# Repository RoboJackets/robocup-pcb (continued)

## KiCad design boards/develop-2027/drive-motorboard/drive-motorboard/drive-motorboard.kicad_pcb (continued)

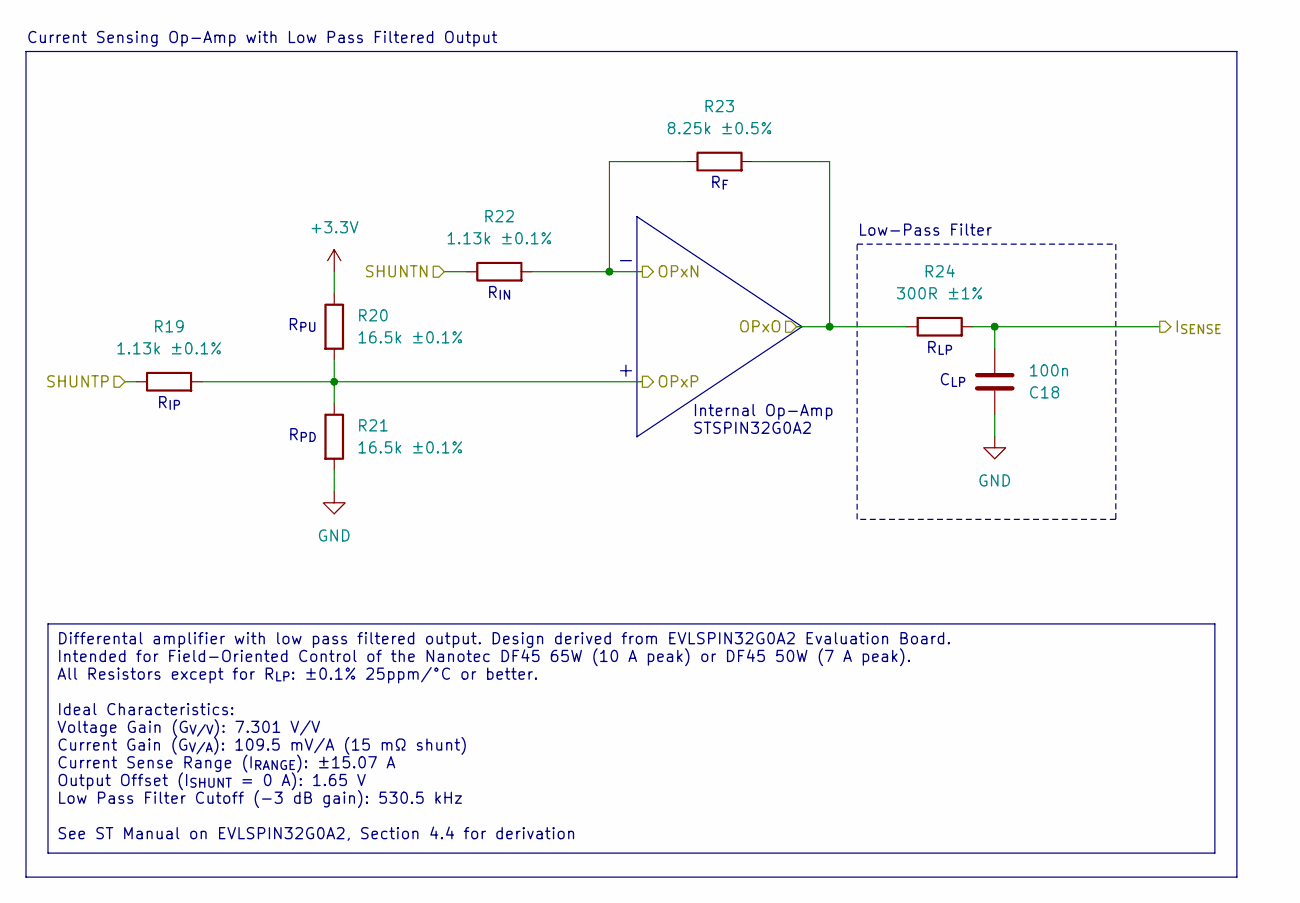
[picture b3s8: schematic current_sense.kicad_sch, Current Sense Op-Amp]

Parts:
C18: 100n; C_0402_1005Metric; Manufacturer P/N CL05B102KB5NNNC
R19, R22: 1.13k ±0.1%; R_0402_1005Metric; Manufacturer P/N RT0402BRD071K13L
R20, R21: 16.5k ±0.1%; R_0402_1005Metric; Manufacturer P/N RT0402BRD0716K5L
R23: 8.25k ±0.5%; R_0201_0603Metric; Manufacturer P/N RC0201DR-078K25L
R24: 300R ±1%; R_0201_0603Metric; Manufacturer P/N RC0201FR-07300RL

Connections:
+3.3V: R20.1; also elsewhere on the board
/Motor Controller/Current Sensing/OPxN: R22.2, R23.1; also elsewhere on the board
/Motor Controller/Current Sensing/OPxO: R23.2, R24.1; also elsewhere on the board
/Motor Controller/Current Sensing/OPxP: R19.2, R20.2, R21.1; also elsewhere on the board
/Motor Controller/I_{SENSE}: C18.2, R24.2; also elsewhere on the board
/Motor Controller/SHUNTN: R22.1; also elsewhere on the board
/Motor Controller/SHUNTP: R19.1; also elsewhere on the board
GND: C18.1, R21.2; also elsewhere on the board

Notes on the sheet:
R_{PU}
C_{LP}
Low-Pass Filter
R_{F}
R_{PD}
R_{IP}
Current Sensing Op-Amp with Low Pass Filtered Output
Internal Op-Amp STSPIN32G0A2
R_{LP}
R_{IN}
Differental amplifier with low pass filtered output. Design derived from EVLSPIN32G0A2 Evaluation Board. Intended for Field-Oriented Control of the Nanotec DF45 65W (10 A peak) or DF45 50W (7 A peak). All Resistors except for R_{LP}: ±0.1% 25ppm/°C or better. Ideal Characteristics: Voltage Gain (G_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

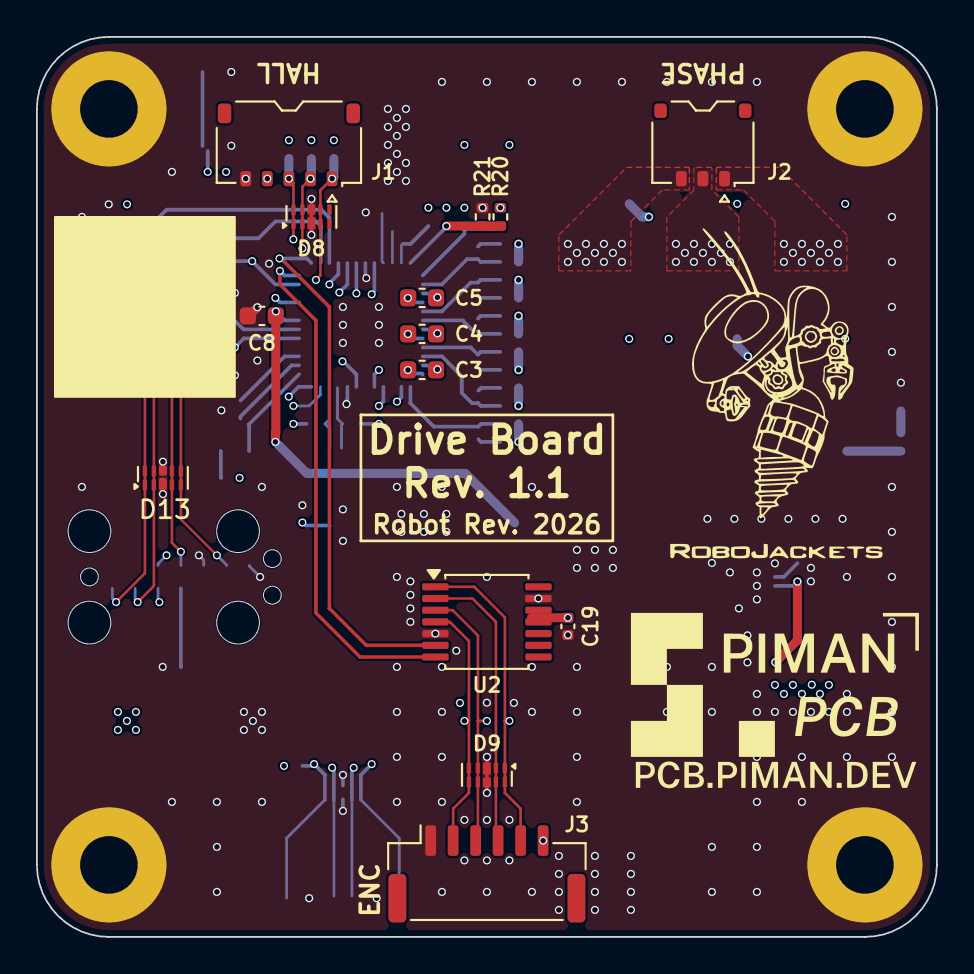
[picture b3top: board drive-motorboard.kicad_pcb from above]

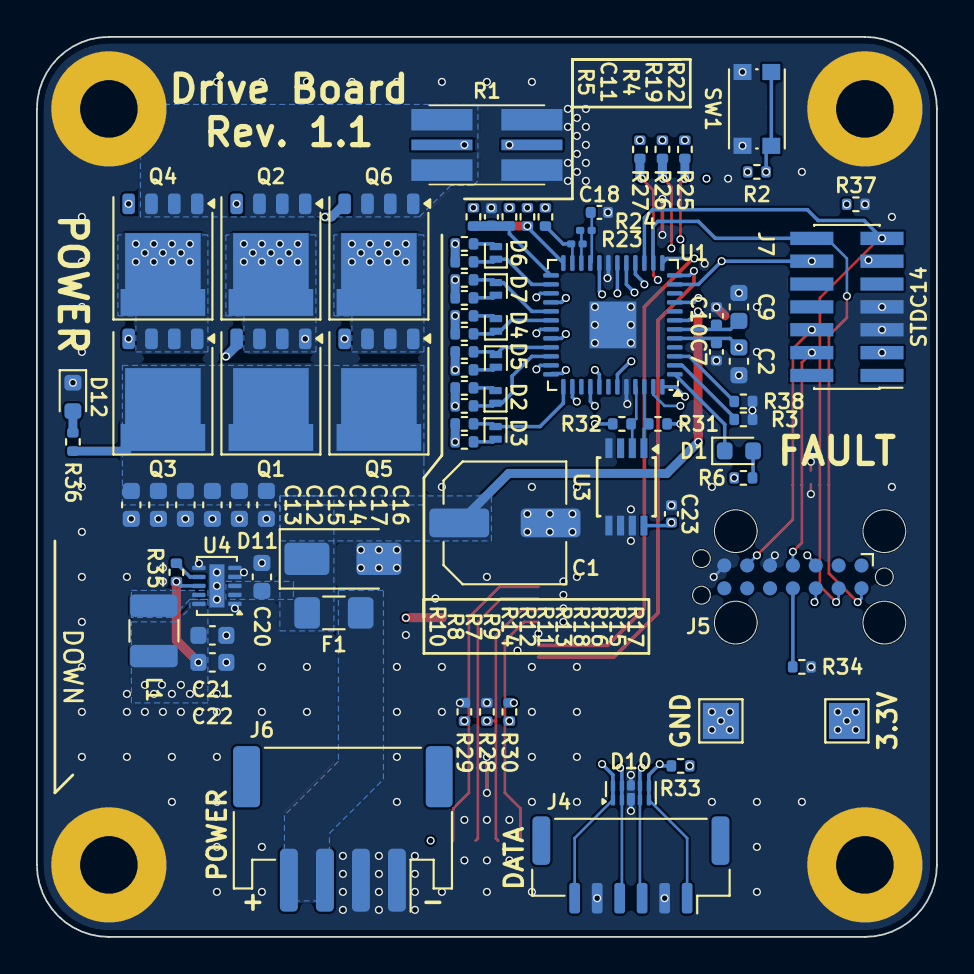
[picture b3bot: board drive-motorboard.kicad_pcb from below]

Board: 6 copper layers, 50.0 x 50.0 mm, 99 parts (81 on the bottom side), 66 nets.

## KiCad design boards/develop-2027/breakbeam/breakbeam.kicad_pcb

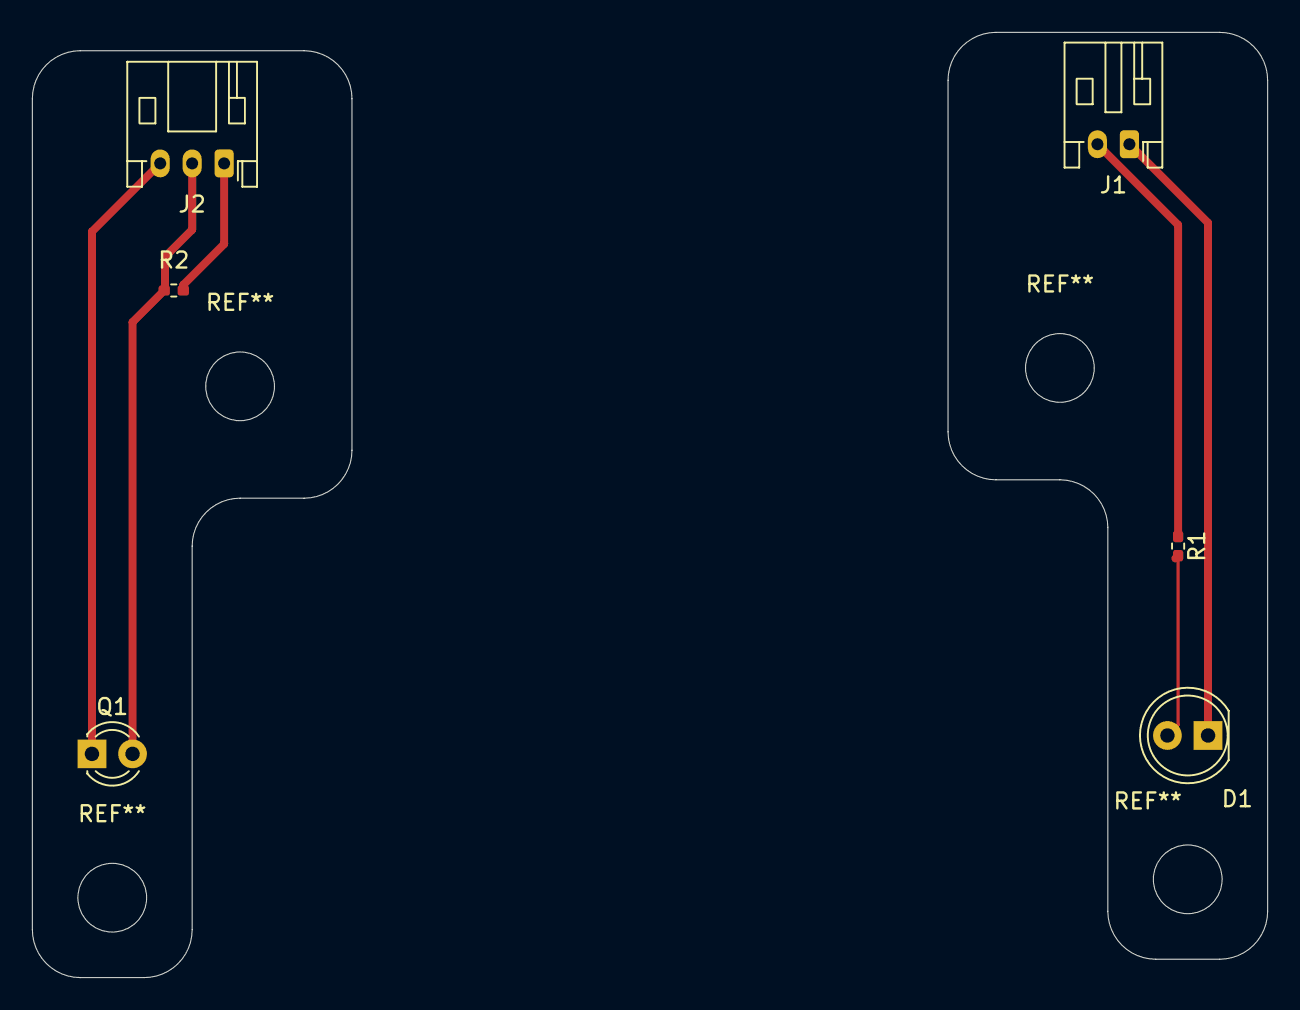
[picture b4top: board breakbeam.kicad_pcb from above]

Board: 2 copper layers, 77.3 x 59.2 mm, 6 parts (0 on the bottom side), 6 nets.

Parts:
D1: LED; LED_D5.0mm
J1: Conn_01x02; JST_PH_S2B-PH-K_1x02_P2.00mm_Horizontal
J2: Conn_01x03; JST_PH_S3B-PH-K_1x03_P2.00mm_Horizontal
Q1: TEPT4400; LED_D3.0mm_Clear
R1: 100; R_0402_1005Metric_Pad0.72x0.64mm_HandSolder
R2: 100k; R_0402_1005Metric_Pad0.72x0.64mm_HandSolder

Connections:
unnamed: D1.2 (A), R1.2
unnamed: D1.1 (K), J1.1
unnamed: J1.2, R1.1
unnamed: J2.1, R2.1
unnamed: J2.2, Q1.2 (E), R2.2
unnamed: J2.3, Q1.1 (C)

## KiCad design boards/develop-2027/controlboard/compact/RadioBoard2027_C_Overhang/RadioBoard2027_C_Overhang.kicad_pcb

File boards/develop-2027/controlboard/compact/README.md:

# Compact board set (ControlBoard2027_C4L2 + 30 x 40 radio)

The compact set is the active 2027 robot electronics design: a 120 x 60 mm controlboard with an STM32H723 and a
30 x 40 mm ESP32-C5 radio that plugs straight onto it. It replaces the prototype set in `../prototype/` (kept for
reference only); every difference is listed in [docs/PROTOTYPE_TO_COMPACT.md](docs/PROTOTYPE_TO_COMPACT.md).

**The controlboard being built is ControlBoard2027_C4L2.** ControlBoard2027_C (6 layers) and ControlBoard2027_C4L
(the first 4-layer copy) are earlier iterations of the same circuit, kept for reference in `archive/`.

| Board | Folder | Size, layers | Main parts |
|---|---|---|---|
| **ControlBoard2027_C4L2** | [ControlBoard2027_C4L2/](ControlBoard2027_C4L2/) | 120 x 60 mm, 4 layers, JLC04161H-3313 1.6 mm | the board being built; same circuit as the C with the connector groups re-placed and most MCU pins moved (PROTOTYPE_TO_COMPACT.md §1.8) |
| ControlBoard2027_C (archived) | [archive/ControlBoard2027_C/](archive/ControlBoard2027_C/) | 120 x 60 mm, 6 layers, JLC06161H-3313E 1.6 mm | STM32H723ZGT6, LSM6DSV320X IMU, microSD, USB-C, 4 motor + dribbler SPI ports, kicker / expansion I2C, powerboard input, DotStar LEDs, OLED socket |
| RadioBoard2027_C_Inboard | [RadioBoard2027_C_Inboard/](RadioBoard2027_C_Inboard/) | 30 x 40 mm, 4 layers, JLC04161H-3313 1.6 mm | ESP32-C5-WROOM-1U, USB-C, power mux + supervisor |
| RadioBoard2027_C_Overhang | [RadioBoard2027_C_Overhang/](RadioBoard2027_C_Overhang/) | 30 x 40 mm, 4 layers, JLC04161H-3313 1.6 mm | same circuit as Inboard |

## Which files are authoritative

1. The KiCad files in each board folder (`.kicad_sch`, `.kicad_pcb`, `.kicad_dru`, `lib/`, `footprints/`). They
   always win.
2. The documents below, which were checked against those files on 2026-11-07; the C4L2 and radio content was
   re-checked on 2026-11-21.

Positions in all documents are in mm from the top-left corner of the board's own outline, x right, y down. In the
board files that corner is at (49.475, 49.475) on the controlboard and (97.0, 100.0) on the radios.

| Document | For | Content |
|---|---|---|
| [docs/INTERFACE.md](docs/INTERFACE.md) | everyone | J9 / J2 board-to-board pin table, mating rule, positions, standoffs, stack height, keep-outs, link timing; controlboard external connector pinouts and what mating boards must use |
| [docs/FIRMWARE.md](docs/FIRMWARE.md) | firmware | STM32 and ESP32-C5 pin maps, clocks, GPIO speed rules, IMU orientation, power switchover, bring-up checklist |
| [docs/PROTOTYPE_TO_COMPACT.md](docs/PROTOTYPE_TO_COMPACT.md) | reviewers, firmware | every change from the prototype, part by part, with reasons |
| [ControlBoard2027_C4L2/README_BEFORE_ORDERING.md](ControlBoard2027_C4L2/README_BEFORE_ORDERING.md) | whoever orders | checklist and sign-off before the C4L2 order |
| [ControlBoard2027_C4L2/DESIGN_NOTES.md](ControlBoard2027_C4L2/DESIGN_NOTES.md), [TODO.txt](ControlBoard2027_C4L2/TODO.txt) | reviewers | controlboard design reasoning, stackup, lengths, rules, deviations, audits; open items |
| [archive/ControlBoard2027_C/DESIGN_NOTES.md](archive/ControlBoard2027_C/DESIGN_NOTES.md), [archive/ControlBoard2027_C4L/DESIGN_NOTES.md](archive/ControlBoard2027_C4L/DESIGN_NOTES.md) | reference | the earlier 6-layer and first 4-layer controlboards (archived) |
| [datasheets/](datasheets/) (sources: [../prototype/ControlBoard2027/datasheets/SOURCES.md](../prototype/ControlBoard2027/datasheets/SOURCES.md)) | everyone | local datasheet copies the designs were checked against |
| [RadioBoard2027_C_Inboard/DESIGN_NOTES.md](RadioBoard2027_C_Inboard/DESIGN_NOTES.md), [TODO.txt](RadioBoard2027_C_Inboard/TODO.txt) | reviewers | Inboard radio design notes; open items |
| [RadioBoard2027_C_Overhang/DESIGN_NOTES.md](RadioBoard2027_C_Overhang/DESIGN_NOTES.md), [TODO.txt](RadioBoard2027_C_Overhang/TODO.txt) | reviewers | Overhang radio design notes; open items |

Diagrams:
- [RadioBoard2027_C_Inboard/docs/board_map.svg](RadioBoard2027_C_Inboard/docs/board_map.svg) and
  [RadioBoard2027_C_Overhang/docs/board_map.svg](RadioBoard2027_C_Overhang/docs/board_map.svg): radio buttons, LEDs,
  USB, test pads and the J2 pin map.

## BOM

The bills of materials are in each board's `bom/` folder: [ControlBoard2027_C4L2/bom/](ControlBoard2027_C4L2/bom/),
[RadioBoard2027_C_Inboard/bom/](RadioBoard2027_C_Inboard/bom/) and
[RadioBoard2027_C_Overhang/bom/](RadioBoard2027_C_Overhang/bom/). Each folder has a full BOM with sourcing and stock,
the JLCPCB upload file, a list of the parts to order separately (Digi-Key / Mouser), and a README with the stock date,
board-set limits, substitutions and open issues. The JLCPCB upload file is generated from the schematic fields.
The LDOs (CB U7, radio U4) are Microchip MCP1826S-3302E/DB (the AP7361C-33E-13 was out of stock everywhere on
2026-11-07). The LSHM mezzanine (CB J9, radio J2) is JLCPCB-assembled as C3643542: 37 at JLCPCB on 2026-11-07, two
per board set, so 18 board sets.

## Folder map

| Path | Content |
|---|---|
| `README.md` | this file |
| `docs/` | set-level documents (INTERFACE, FIRMWARE, PROTOTYPE_TO_COMPACT) |
| `datasheets/` | datasheet PDFs for all compact boards (copied from `../prototype/ControlBoard2027/datasheets/` on 2026-11-21; download sources in that folder's `SOURCES.md`) |
| `ControlBoard2027_C4L2/` | controlboard being built: KiCad project, `DESIGN_NOTES.md`, `TODO.txt`, `README_BEFORE_ORDERING.md`, `bom/`, `mechanical/`, `lib/`, `footprints/` |
| `archive/` | earlier controlboard iterations, kept for reference: `ControlBoard2027_C/` (6 layers) and `ControlBoard2027_C4L/` (first 4-layer copy). Not maintained; their relative links point to their old location |
| `RadioBoard2027_C_Inboard/` | Inboard radio KiCad project, `DESIGN_NOTES.md`, `TODO.txt`, `docs/board_map.svg`, `lib/` |
| `RadioBoard2027_C_Overhang/` | Overhang radio KiCad project, `DESIGN_NOTES.md`, `TODO.txt`, `docs/board_map.svg`, `lib/` |

## The two radio variants

Both radios have the same schematic (identical netlists), the same outline, the same J2 position and pinout and the
same standoff holes, so either one fits the same controlboard. Both accept the ESP32-C5-WROOM-1U (primary build,
u.FL connector with an external antenna) and the ESP32-C5-WROOM-1 (fallback, PCB antenna) on one dual footprint.
They differ only in where the module sits, which matters only for a WROOM-1 build:

| | Inboard | Overhang |
|---|---|---|
| Module position | (19.85, 17.9), antenna end 1 mm inside the north edge | (19.85, 11.5), antenna end past the north edge |
| WROOM-1 antenna | inside the radio outline, over the controlboard (CB x 46.1-66.1, y 0-7.5, where the CB has copper) | 5.45 mm past the radio and controlboard front edge (keep-out 6.4 mm) |
| Link length on the radio (matched) | 19.934 mm | 14.079 mm |
| USB pair skew | orientation B -0.001 mm, A +5.94 mm (about 40 ps; a both-orientation match does not fit beside SW2; negligible at Full Speed; one-orientation match accepted per the user's instruction) | -0.001 / +0.000 mm in both orientations |
| Buttons | RESET on the west edge, BOOT on the south edge | RESET and BOOT side by side near the south edge |

With the WROOM-1U both variants work the same. Pick the Overhang if a WROOM-1 build is likely and the robot has room
in front of the board; pick the Inboard if nothing may stick out.

## Status (2026-11-07; C4L2 and radios re-checked 2026-11-21)

All boards are placed and routed. Checks on the saved repo files (kicad-cli, schematic parity on):

| Board | DRC errors | Unconnected | Parity | DRC warnings | ERC |
|---|---|---|---|---|---|
| ControlBoard2027_C4L2 (2026-11-21, zones refilled) | 0 | 0 | 0 | 15, all intended: 6 courtyard (J13 OLED module over J1 / J2 / U3 / D1 / F1, J9 / U2), 2 NPTH in courtyard (J2 under J13), 7 silk overlap (C4L2 DESIGN_NOTES §1) | 1 error, intended: U2 VCAP pins 71 / 106 tied |
| ControlBoard2027_C (2026-11-07, reference) | 0 | 0 | 0 | 13, all intended: 11 courtyard overlaps (J9 / U2 margin 0.02 mm; ten low parts under the raised OLED module J13) and 2 J2 locating holes under J13 | 1 error, intended: U2 VCAP pins 71 / 106 tied (power output to power output) |
| RadioBoard2027_C_Inboard | 0 | 0 | 0 | 0 | 0 |
| RadioBoard2027_C_Overhang | 0 | 0 | 0 | 0 | 0 |

Matched groups (re-measured with the length scripts on the saved boards):

| Group | Result |
|---|---|
| C4L2 radio SPI1 (to J9) | SCK 15.200, MOSI 15.400, MISO 15.481, CS 14.478 mm (within 1 mm of SCK) |
| C4L2 SDMMC2 | 67.07-67.65 mm, CK 67.16 mm (pin to pin, independent audit 2026-11-20) |
| CB radio SPI3 (to J9), ControlBoard2027_C | 14.860-14.861 mm |
| CB SDMMC2, ControlBoard2027_C | 62.231-62.496 mm (D1 +0.264 mm, within 1 mm) |
| CB motor SPI1 / SPI2 / dribbler SPI4, LED SPI6, ControlBoard2027_C | each connector within 0.001 mm, except J6 MOSI -0.222 mm |
| CB USB, ControlBoard2027_C | 0.000 mm skew in both plug orientations |
| Radio link SCK / MOSI / MISO / CS | Inboard 19.934 mm, Overhang 14.079 mm, spread 0.000 mm |
| Radio USB | see the variant table above |

Each board's independent adversarial audits are summarised in the Review history appendix of its DESIGN_NOTES. The
pre-fabrication audit of the C4L2 and both radios (2026-11-20) found no open critical item; its summary is in C4L2
DESIGN_NOTES §1 and the radio TODOs.

### Open before ordering

Details and the full lists are in each board's TODO.txt.

- **All boards:** confirm the impedance widths in JLC's calculator and order with impedance control; independent
  re-audit of the last changed areas (CB back-edge connectors and audit fixes; Overhang USB-skew changes; Inboard
  after any further change), then refill zones, DRC with parity, ERC and the length scripts again; generate the
  placement files (the BOMs exist, see above); re-check stock (LSHM C3643542 is the limiting JLCPCB part); parts not
  stocked at JLCPCB must be sourced separately (radios: U1, hand-soldered, and ANT1; every CB part is JLC-assembled).
- **Controlboard:** agree J15 (powerboard), J10 (kicker) and J11 / J12 (expansion) pinouts with the mating boards; J4-J8 are
  settled (drive motors on a reversed GH cable, dribbler straight, INTERFACE.md); choose the OLED module; confirm the DotStar footprint (top-view drawing).
- **Radios:** decide the antenna (FXP831 5 GHz gain above the module's certified gain; Inboard WROOM-1 fallback sits
  over CB copper); keep the CB +3V3 load at about 0.8 A or less including the radio and measure +3V3 at J9 during TX
  (radio TODO 1.0); the radio USB-C is probably blocked by the speaker board (radio TODO 1.0a); fab notes for tented and plugged vias and the J2 paste-in-hole stencil; check the TPD4E05U06 land
  pattern against TI's drawing.

Fabrication outputs (gerbers, CPL) are not generated for the compact set; the BOMs are in each board's `bom/`.

## Interface rule

J9 / J2 and the standoff holes are shared by three projects. Change them in all three together and re-run the
mating check; see [docs/INTERFACE.md](docs/INTERFACE.md) §6.

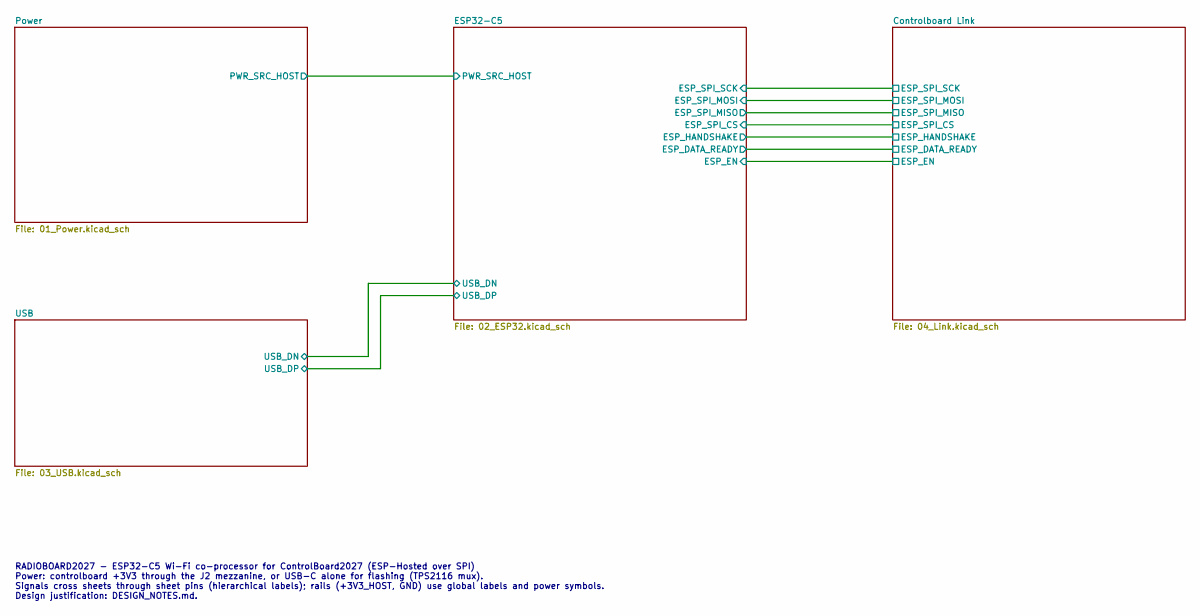
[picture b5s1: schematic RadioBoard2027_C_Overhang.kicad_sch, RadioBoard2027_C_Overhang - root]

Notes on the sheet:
RADIOBOARD2027 - ESP32-C5 Wi-Fi co-processor for ControlBoard2027 (ESP-Hosted over SPI) Power: controlboard +3V3 through the J2 mezzanine, or USB-C alone for flashing (TPS2116 mux). Signals cross sheets through sheet pins (hierarchical labels); rails (+3V3_HOST, GND) use global labels and power sym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

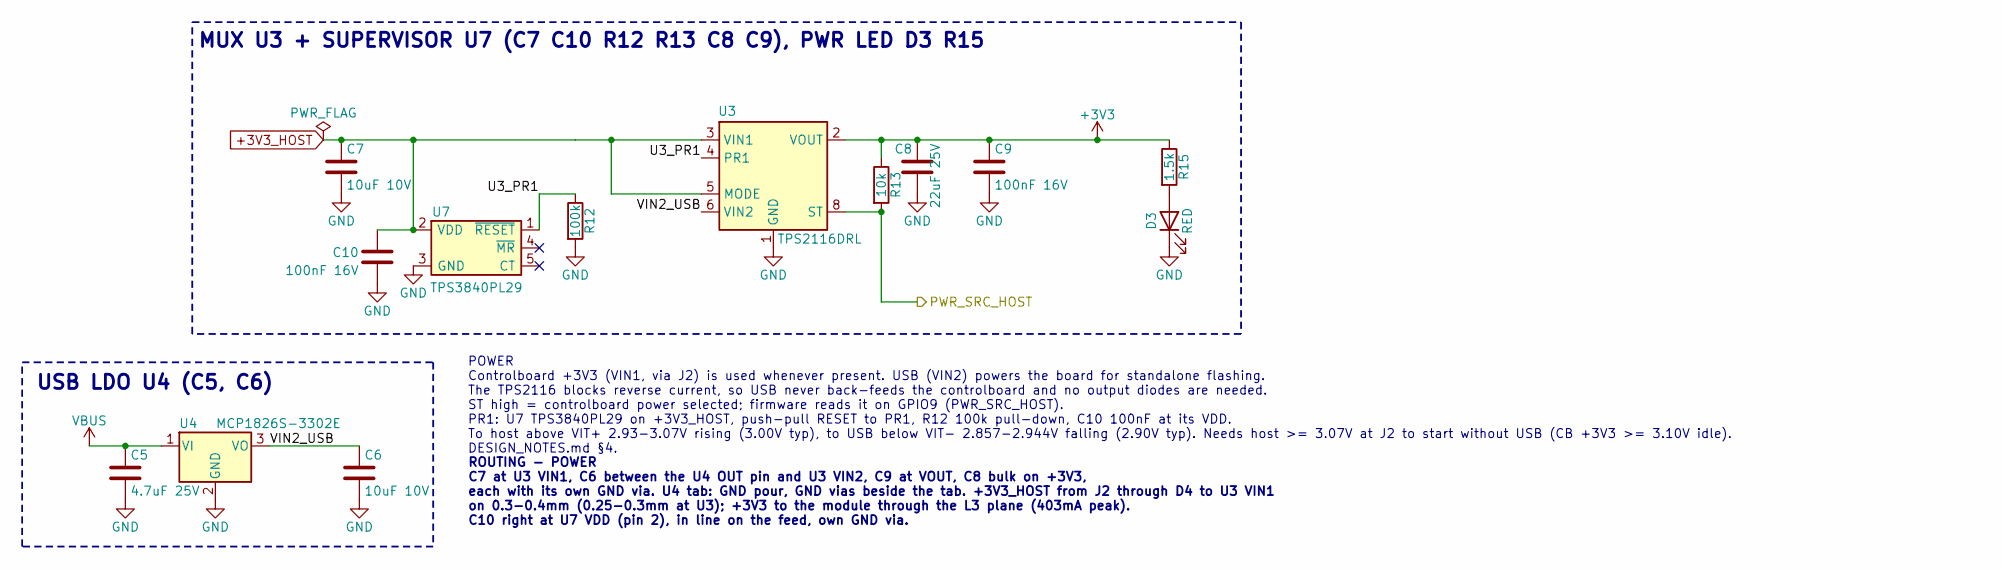
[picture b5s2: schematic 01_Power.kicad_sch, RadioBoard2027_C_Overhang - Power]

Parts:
C5: 4.7uF 25V; C_0805_2012Metric; Rating 25V X5R; MPN Samsung CL21A475KAQNNNE; LCSC C1779
C6, C7: 10uF 10V; C_0603_1608Metric; Rating 10V X5R 10%; MPN Samsung CL10A106KP8NNNC; LCSC C19702
C8: 22uF 25V; C_0805_2012Metric; Rating 25V X5R 20%; MPN Samsung CL21A226MAQNNNE; LCSC C45783
C9, C10: 100nF 16V; C_0402_1005Metric; Rating 16V X7R; MPN Samsung CL05B104KO5NNNC; LCSC C1525
D3: RED; LED_0603_1608Metric; MPN Kingbright APT1608EC; LCSC C5554143
R12: 100k; R_0402_1005Metric; Rating 1%; MPN UNI-ROYAL 0402WGF1003TCE; LCSC C25741
R13: 10k; R_0402_1005Metric; Rating 1%; MPN UNI-ROYAL 0402WGF1002TCE; LCSC C25744
R15: 1.5k; R_0402_1005Metric; Rating 1%; MPN UNI-ROYAL 0402WGF1501TCE; LCSC C25867
U3: TPS2116DRL; SOT-583-8; MPN TI TPS2116DRLR; LCSC C3235557
U4: MCP1826S-3302E; SOT-223-3_TabPin2; Rating 1A, VIN 6.0V max, 3.3V +-2.5%; MPN Microchip MCP1826S-3302E/DB; LCSC C638624
U7: TPS3840PL29; SOT-23-5; Rating VIT- 2.9V +-1.5%, VHYS 75-125mV, 10V VD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; MPN TI TPS3840PL29DBVR; LCSC C1852117

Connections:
+3V3: C8.1, C9.1, R13.1, R15.1, U3.2 (VOUT), U3.7 (VOUT); also elsewhere on the board
+3V3_HOST: C7.1, C10.1, U3.3 (VIN1), U3.5 (MODE), U7.2 (VDD); also elsewhere on the board
/ESP32-C5/PWR_SRC_HOST: R13.2, U3.8 (ST); also elsewhere on the board
/Power/U3_PR1: R12.1, U3.4 (PR1), U7.1 (~RESET)
/Power/VIN2_USB: C6.1, U3.6 (VIN2), U4.3 (VO)
GND: C5.2, C6.2, C7.2, C8.2, C9.2, C10.2, D3.1 (K), R12.2, U3.1 (GND), U4.2 (GND), U7.3 (GND); also elsewhere on the board
unnamed: D3.2 (A), R15.2
VBUS: C5.1, U4.1 (VI); also elsewhere on the board

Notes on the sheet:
MUX U3 + SUPERVISOR U7 (C7 C10 R12 R13 C8 C9), PWR LED D3 R15
USB LDO U4 (C5, C6)
POWER Controlboard +3V3 (VIN1, via J2) is used whenever present. USB (VIN2) powers the board for standalone flashing. The TPS2116 blocks reverse current, so USB never back-feeds the controlboard and no output diodes are needed. ST high = controlboard power selected; firmware reads it on GPIO9 (PWR_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
ROUTING - POWER C7 at U3 VIN1, C6 between the U4 OUT pin and U3 VIN2, C9 at VOUT, C8 bulk on +3V3, each with its own GND via. U4 tab: GND pour, GND vias beside the tab. +3V3_HOST from J2 through D4 to U3 VIN1 on 0.3-0.4mm (0.25-0.3mm at U3); +3V3 to the module through the L3 plane (403mA peak). C10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

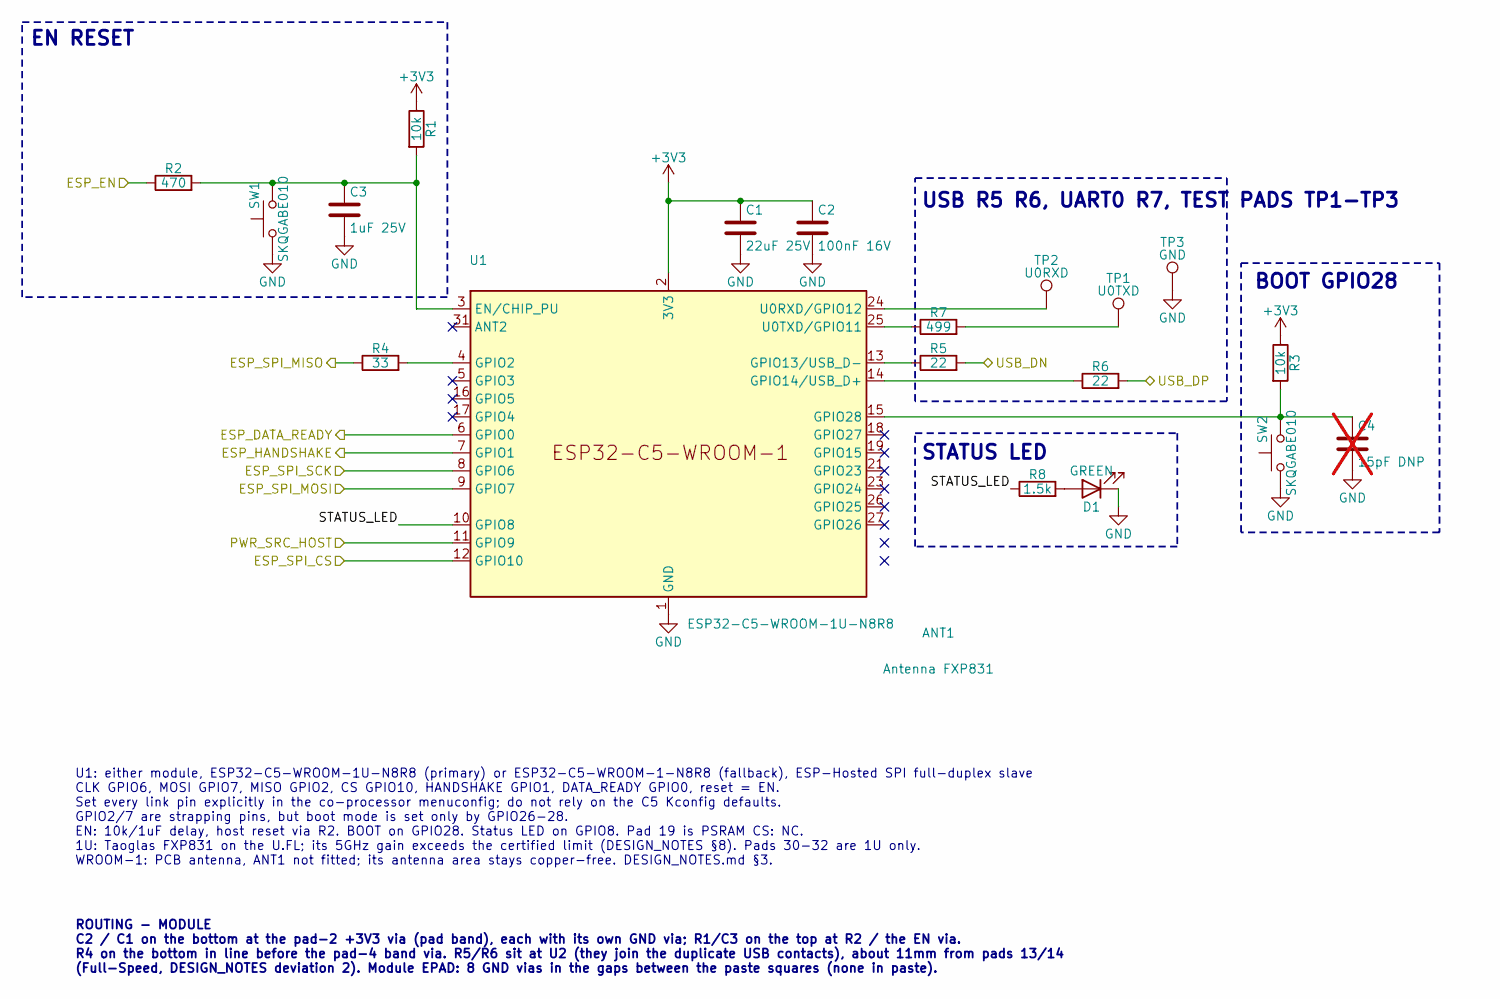
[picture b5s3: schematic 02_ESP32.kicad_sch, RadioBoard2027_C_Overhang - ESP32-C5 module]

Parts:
ANT1: Antenna FXP831; MPN Taoglas FXP831.07.0100C
C1: 22uF 25V; C_0805_2012Metric; Rating 25V X5R 20%; MPN Samsung CL21A226MAQNNNE; LCSC C45783
C2: 100nF 16V; C_0402_1005Metric; Rating 16V X7R; MPN Samsung CL05B104KO5NNNC; LCSC C1525
C3: 1uF 25V; C_0402_1005Metric; Rating 25V X5R; MPN Samsung CL05A105KA5NQNC; LCSC C52923
C4: 15pF DNP; C_0402_1005Metric; Rating 50V C0G; MPN Murata GRM1555C1H150JA01D; not fitted
D1: GREEN; LED_0603_1608Metric; MPN Kingbright APT1608SGC; LCSC C5875754
R1, R3: 10k; R_0402_1005Metric; Rating 1%; MPN UNI-ROYAL 0402WGF1002TCE; LCSC C25744
R2: 470; R_0402_1005Metric; Rating 1%; MPN UNI-ROYAL 0402WGF4700TCE; LCSC C25117
R4: 33; R_0402_1005Metric; Rating 1%; MPN UNI-ROYAL 0402WGF330JTCE; LCSC C25105
R5, R6: 22; R_0402_1005Metric; Rating 1%; MPN UNI-ROYAL 0402WGF220JTCE; LCSC C25092
R7: 499; R_0402_1005Metric; Rating 1%; MPN Yageo RC0402FR-07499RL; LCSC C137970
R8: 1.5k; R_0402_1005Metric; Rating 1%; MPN UNI-ROYAL 0402WGF1501TCE; LCSC C25867
SW1, SW2: SKQGABE010; SW_SPST_SKQG_WithStem; MPN Alps Alpine SKQGABE010; LCSC C115351
TP1: U0TXD; TestPoint_Pad_D1.0mm
TP2: U0RXD; TestPoint_Pad_D1.0mm
TP3: GND; TestPoint_Pad_D1.0mm
U1: ESP32-C5-WROOM-1U-N8R8; ESP32-C5-WROOM-1_1U_DUAL; MPN Espressif ESP32-C5-WROOM-1U-N8R8

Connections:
+3V3: C1.1, C2.1, R1.1, R3.1, U1.2 (3V3); also elsewhere on the board
/Controlboard Link/ESP_DATA_READY: U1.6 (GPIO0); also elsewhere on the board
/Controlboard Link/ESP_EN: R2.1; also elsewhere on the board
/Controlboard Link/ESP_HANDSHAKE: U1.7 (GPIO1); also elsewhere on the board
/Controlboard Link/ESP_SPI_CS: U1.12 (GPIO10); also elsewhere on the board
/Controlboard Link/ESP_SPI_MISO: R4.1; also elsewhere on the board
/Controlboard Link/ESP_SPI_MOSI: U1.9 (GPIO7); also elsewhere on the board
/Controlboard Link/ESP_SPI_SCK: U1.8 (GPIO6); also elsewhere on the board
/ESP32-C5/PWR_SRC_HOST: U1.11 (GPIO9); also elsewhere on the board
/ESP32-C5/STATUS_LED: R8.1, U1.10 (GPIO8)
/USB/USB_DN: R5.2; also elsewhere on the board
/USB/USB_DP: R6.2; also elsewhere on the board
GND: C1.2, C2.2, C3.2, C4.2, D1.1 (K), SW1.1, SW2.1, TP3.1, U1.1 (GND), U1.28 (GND), U1.29 (GND), U1.30 (GND), U1.32 (GND); also elsewhere on the board
unnamed: D1.2 (A), R8.2
unnamed: R7.2, TP1.1
unnamed: C3.1, R1.2, R2.2, SW1.2, U1.3 (EN/CHIP_PU)
unnamed: R4.2, U1.4 (GPIO2)
unnamed: R5.1, U1.13 (GPIO13/USB_D-)
unnamed: R6.1, U1.14 (GPIO14/USB_D+)
unnamed: C4.1, R3.2, SW2.2, U1.15 (GPIO28)
unnamed: TP2.1, U1.24 (U0RXD/GPIO12)
unnamed: R7.1, U1.25 (U0TXD/GPIO11)

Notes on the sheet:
EN RESET
USB R5 R6, UART0 R7, TEST PADS TP1-TP3
BOOT GPIO28
STATUS LED
ROUTING - MODULE C2 / C1 on the bottom at the pad-2 +3V3 via (pad band), each with its own GND via; R1/C3 on the top at R2 / the EN via. R4 on the bottom in line before the pad-4 band via. R5/R6 sit at U2 (they join the duplicate USB contacts), about 11mm from pads 13/14 (Full-Speed, DESIGN_NOTES d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
U1: either module, ESP32-C5-WROOM-1U-N8R8 (primary) or ESP32-C5-WROOM-1-N8R8 (fallback), ESP-Hosted SPI full-duplex slave CLK GPIO6, MOSI GPIO7, MISO GPIO2, CS GPIO10, HANDSHAKE GPIO1, DATA_READY GPIO0, reset = EN. Set every link pin explicitly in the co-processor menuconfig; do not rely on the C5 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

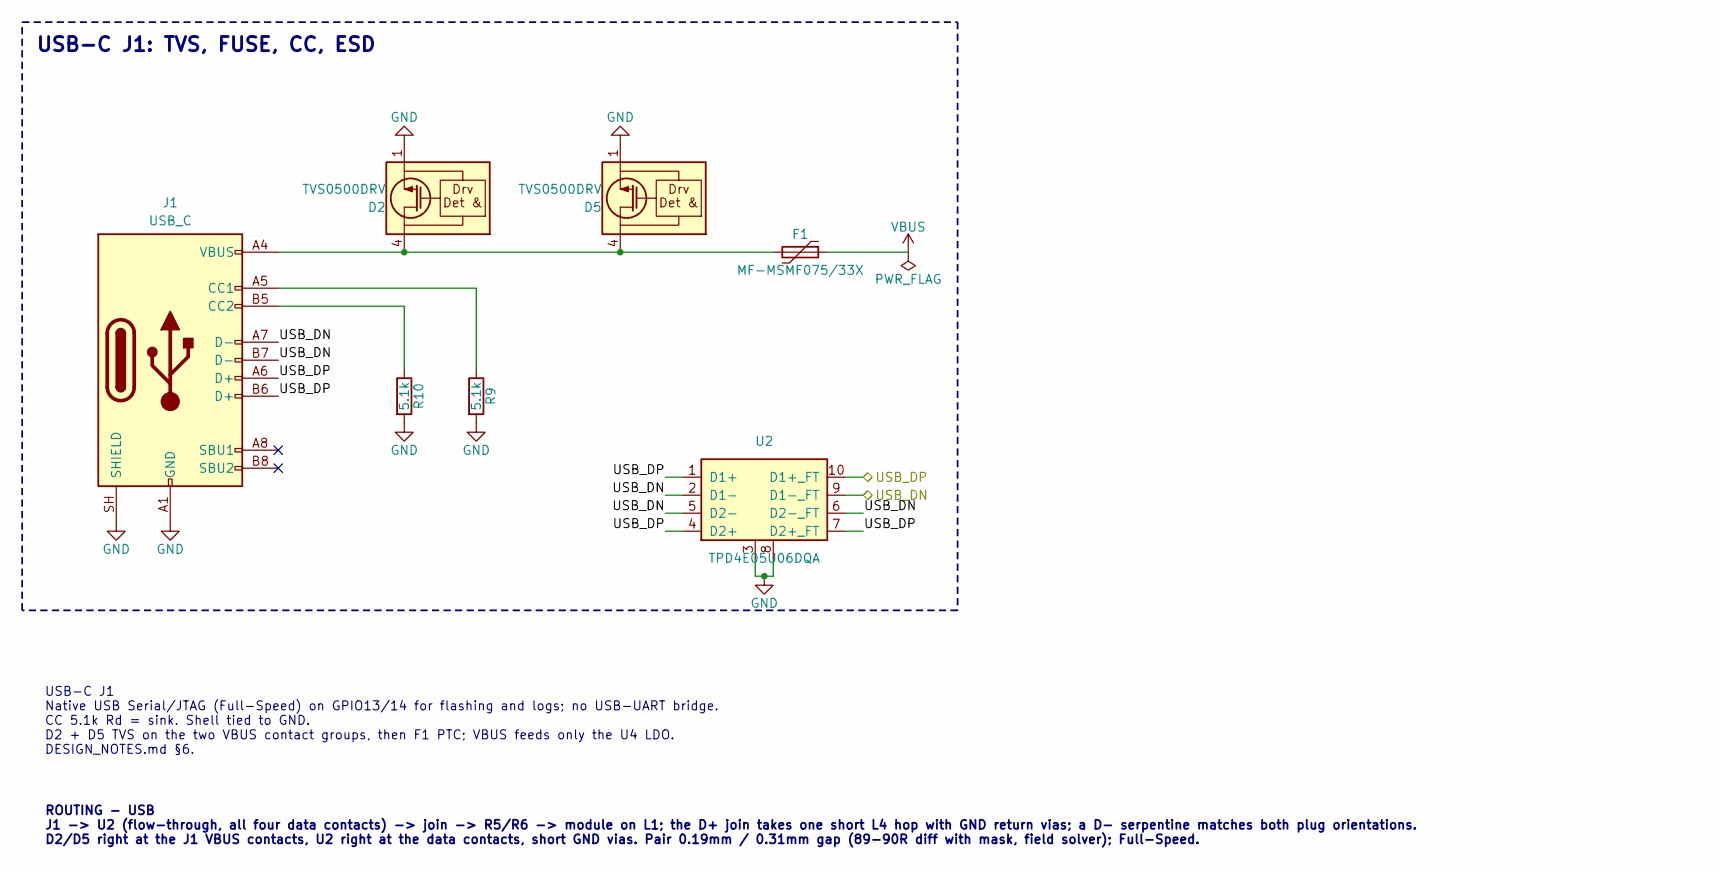
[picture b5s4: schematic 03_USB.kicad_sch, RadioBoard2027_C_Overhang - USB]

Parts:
D2, D5: TVS0500DRV; WSON-6-1EP_2x2mm_P0.65mm_EP1x1.6mm; MPN TI TVS0500DRVR; LCSC C609571
F1: MF-MSMF075/33X; Fuse_1812_4532Metric; Rating Hold 0.75A, trip 1.5A, 33V max, 1812; MPN Bourns MF-MSMF075/33X-2; LCSC C3760814
J1: USB_C; USB_C_Receptacle_GCT_USB4110; MPN GCT USB4110-GF-A; LCSC C5143397
R9, R10: 5.1k; R_0402_1005Metric; Rating 1%; MPN UNI-ROYAL 0402WGF5101TCE; LCSC C25905
U2: TPD4E05U06DQA; USON-10_2.5x1.0mm_P0.5mm; MPN TI TPD4E05U06DQAR; LCSC C138714

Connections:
/USB/USB_DN: J1.A7 (D-), J1.B7 (D-), U2.2 (D1-), U2.5 (D2-), U2.6 (D2-_FT), U2.9 (D1-_FT); also elsewhere on the board
/USB/USB_DP: J1.A6 (D+), J1.B6 (D+), U2.1 (D1+), U2.4 (D2+), U2.7 (D2+_FT), U2.10 (D1+_FT); also elsewhere on the board
GND: D2.1 (GND), D2.2 (GND), D2.3 (GND), D2.7 (GND), D5.1 (GND), D5.2 (GND), D5.3 (GND), D5.7 (GND), J1.A1 (GND), J1.A12 (GND), J1.B1 (GND), J1.B12 (GND), J1.SH (SHIELD), R9.2, R10.2, U2.3, U2.8; also elsewhere on the board
unnamed: D2.4 (IN), D2.5 (IN), D2.6 (IN), D5.4 (IN), D5.5 (IN), D5.6 (IN), F1.2, J1.A4 (VBUS), J1.A9 (VBUS), J1.B4 (VBUS), J1.B9 (VBUS)
unnamed: J1.A5 (CC1), R9.1
unnamed: J1.B5 (CC2), R10.1
VBUS: F1.1; also elsewhere on the board

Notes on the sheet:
USB-C J1: TVS, FUSE, CC, ESD
USB-C J1 Native USB Serial/JTAG (Full-Speed) on GPIO13/14 for flashing and logs; no USB-UART bridge. CC 5.1k Rd = sink. Shell tied to GND. D2 + D5 TVS on the two VBUS contact groups, then F1 PTC; VBUS feeds only the U4 LDO. DESIGN_NOTES.md §6.
ROUTING - USB J1 -> U2 (flow-through, all four data contacts) -> join -> R5/R6 -> module on L1; the D+ join takes one short L4 hop with GND return vias; a D- serpentine matches both plug orientations. D2/D5 right at the J1 VBUS contacts, U2 right at the data contacts, short GND vias. Pair 0.19mm / 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

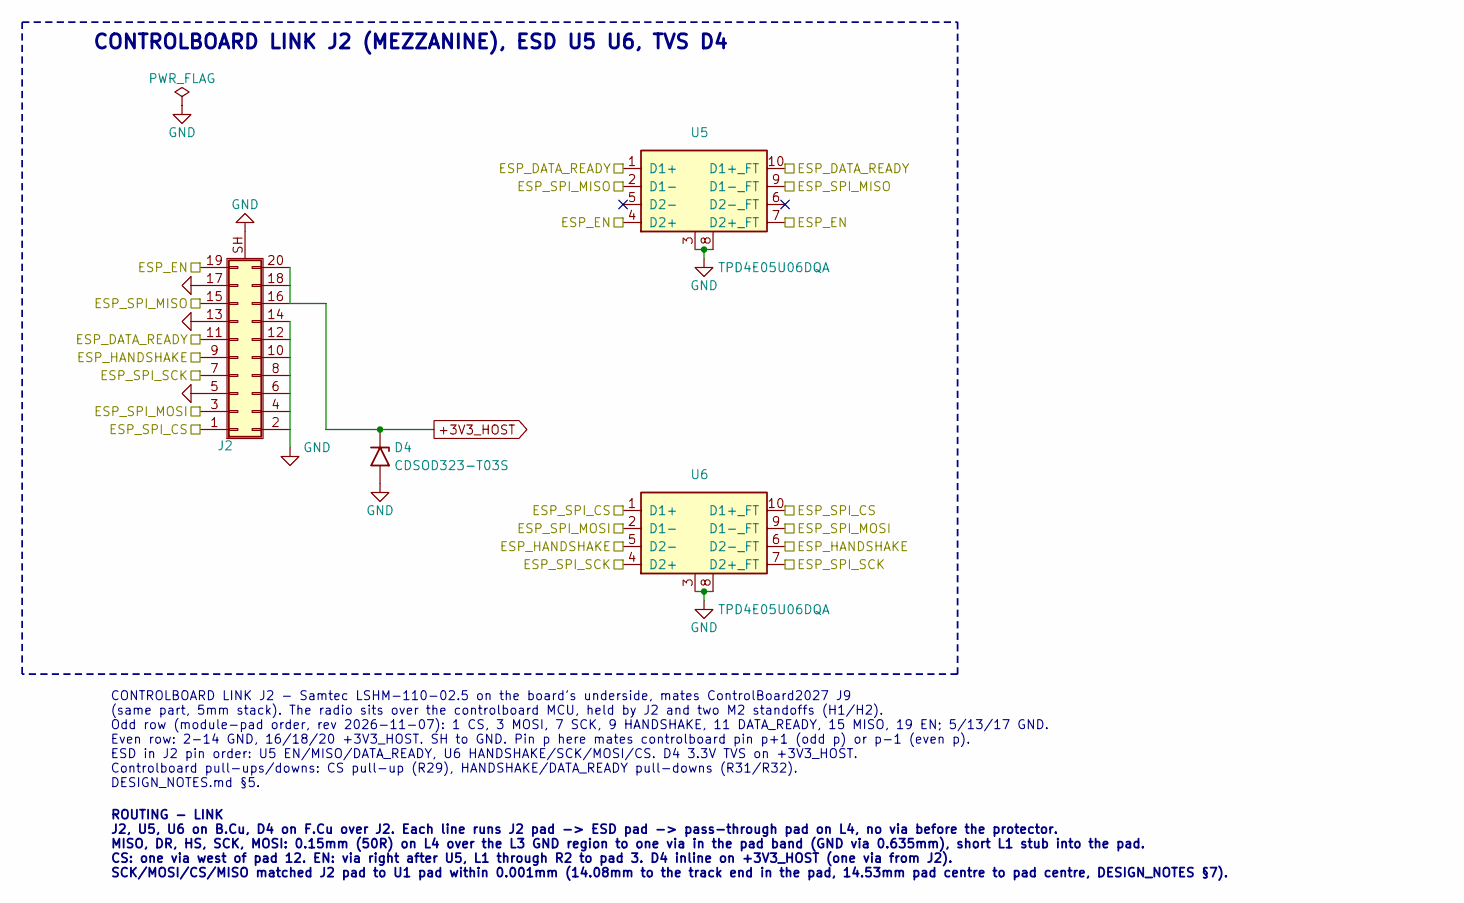
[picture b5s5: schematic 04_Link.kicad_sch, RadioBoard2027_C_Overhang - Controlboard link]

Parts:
D4: CDSOD323-T03S; D_SOD-323_Bourns; Rating 3.3V VRWM, 4.0V VBR min, 500W 8/20us; MPN Bourns CDSOD323-T03S; LCSC C3702214
J2: RADIO_MEZZ; Samtec_LSHM-110-xx.x-x-DV-S_2x10-1SH_P0.50mm_Vertical_PIH; MPN Samtec LSHM-110-02.5-L-DV-A-S-K-TR; LCSC C3643542
U5, U6: TPD4E05U06DQA; USON-10_2.5x1.0mm_P0.5mm; MPN TI TPD4E05U06DQAR; LCSC C138714

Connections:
+3V3_HOST: D4.1 (K), J2.16, J2.18, J2.20; also elsewhere on the board
/Controlboard Link/ESP_DATA_READY: J2.11, U5.1 (D1+), U5.10 (D1+_FT); also elsewhere on the board
/Controlboard Link/ESP_EN: J2.19, U5.4 (D2+), U5.7 (D2+_FT); also elsewhere on the board
/Controlboard Link/ESP_HANDSHAKE: J2.9, U6.5 (D2-), U6.6 (D2-_FT); also elsewhere on the board
/Controlboard Link/ESP_SPI_CS: J2.1, U6.1 (D1+), U6.10 (D1+_FT); also elsewhere on the board
/Controlboard Link/ESP_SPI_MISO: J2.15, U5.2 (D1-), U5.9 (D1-_FT); also elsewhere on the board
/Controlboard Link/ESP_SPI_MOSI: J2.3, U6.2 (D1-), U6.9 (D1-_FT); also elsewhere on the board
/Controlboard Link/ESP_SPI_SCK: J2.7, U6.4 (D2+), U6.7 (D2+_FT); also elsewhere on the board
GND: D4.2 (A), J2.2, J2.4, J2.5, J2.6, J2.8, J2.10, J2.12, J2.13, J2.14, J2.17, J2.SH (Shield), U5.3, U5.8, U6.3, U6.8; also elsewhere on the board

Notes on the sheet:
CONTROLBOARD LINK J2 (MEZZANINE), ESD U5 U6, TVS D4
CONTROLBOARD LINK J2 - Samtec LSHM-110-02.5 on the board's underside, mates ControlBoard2027 J9 (same part, 5mm stack). The radio sits over the controlboard MCU, held by J2 and two M2 standoffs (H1/H2). Odd row (module-pad order, rev 2026-11-07): 1 CS, 3 MOSI, 7 SCK, 9 HANDSHAKE, 11 DATA_READY, 15 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
ROUTING - LINK J2, U5, U6 on B.Cu, D4 on F.Cu over J2. Each line runs J2 pad -> ESD pad -> pass-through pad on L4, no via before the protector. MISO, DR, HS, SCK, MOSI: 0.15mm (50R) on L4 over the L3 GND region to one via in the pad band (GND via 0.635mm), short L1 stub into the pad. CS: one via we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

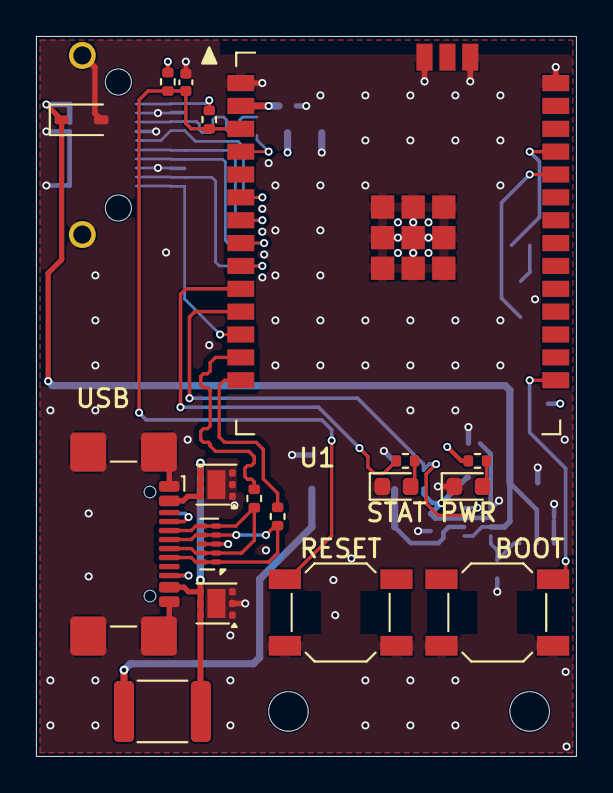
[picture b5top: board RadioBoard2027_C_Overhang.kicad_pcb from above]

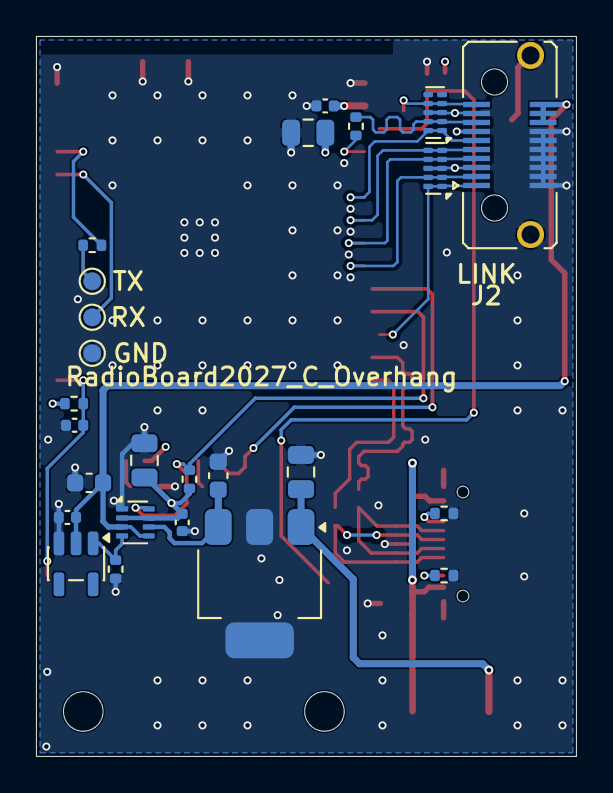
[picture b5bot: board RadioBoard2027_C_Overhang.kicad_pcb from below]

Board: 4 copper layers, 30.0 x 40.0 mm, 45 parts (25 on the bottom side), 30 nets.

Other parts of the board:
H1, H2: MountingHole M2; MountingHole_2.2mm_M2

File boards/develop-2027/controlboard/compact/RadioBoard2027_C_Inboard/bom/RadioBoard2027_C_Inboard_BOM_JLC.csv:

Comment,Designator,Footprint,LCSC Part #
22uF 25V,"C1,C8",C_0805_2012Metric,C45783
100nF 16V,"C2,C9,C10",C_0402_1005Metric,C1525
1uF 25V,C3,C_0402_1005Metric,C52923
4.7uF 25V,C5,C_0805_2012Metric,C1779
10uF 10V,"C6,C7",C_0603_1608Metric,C19702
GREEN,D1,LED_0603_1608Metric,C5875754
TVS0500DRV,"D2,D5",WSON-6-1EP_2x2mm_P0.65mm_EP1x1.6mm,C609571
RED,D3,LED_0603_1608Metric,C5554143
CDSOD323-T03S,D4,D_SOD-323_Bourns,C3702214
MF-MSMF075/33X,F1,Fuse_1812_4532Metric,C3760814
USB_C,J1,USB_C_Receptacle_GCT_USB4110,C5143397
RADIO_MEZZ,J2,Samtec_LSHM-110-xx.x-x-DV-S_2x10-1SH_P0.50mm_Vertical_PIH,C3643542
10k,"R1,R3,R13",R_0402_1005Metric,C25744
470,R2,R_0402_1005Metric,C25117
33,R4,R_0402_1005Metric,C25105
22,"R5,R6",R_0402_1005Metric,C25092
499,R7,R_0402_1005Metric,C137970
1.5k,"R8,R15",R_0402_1005Metric,C25867
5.1k,"R9,R10",R_0402_1005Metric,C25905
100k,R12,R_0402_1005Metric,C25741
SKQGABE010,"SW1,SW2",SW_SPST_SKQG_WithStem,C115351
TPD4E05U06DQA,"U2,U5,U6",USON-10_2.5x1.0mm_P0.5mm,C138714
TPS2116DRL,U3,SOT-583-8,C3235557
MCP1826S-3302E,U4,SOT-223-3_TabPin2,C638624
TPS3840PL29,U7,SOT-23-5,C1852117
